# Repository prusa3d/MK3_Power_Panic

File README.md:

# MK3 Power Panic
KiCad PCB layout

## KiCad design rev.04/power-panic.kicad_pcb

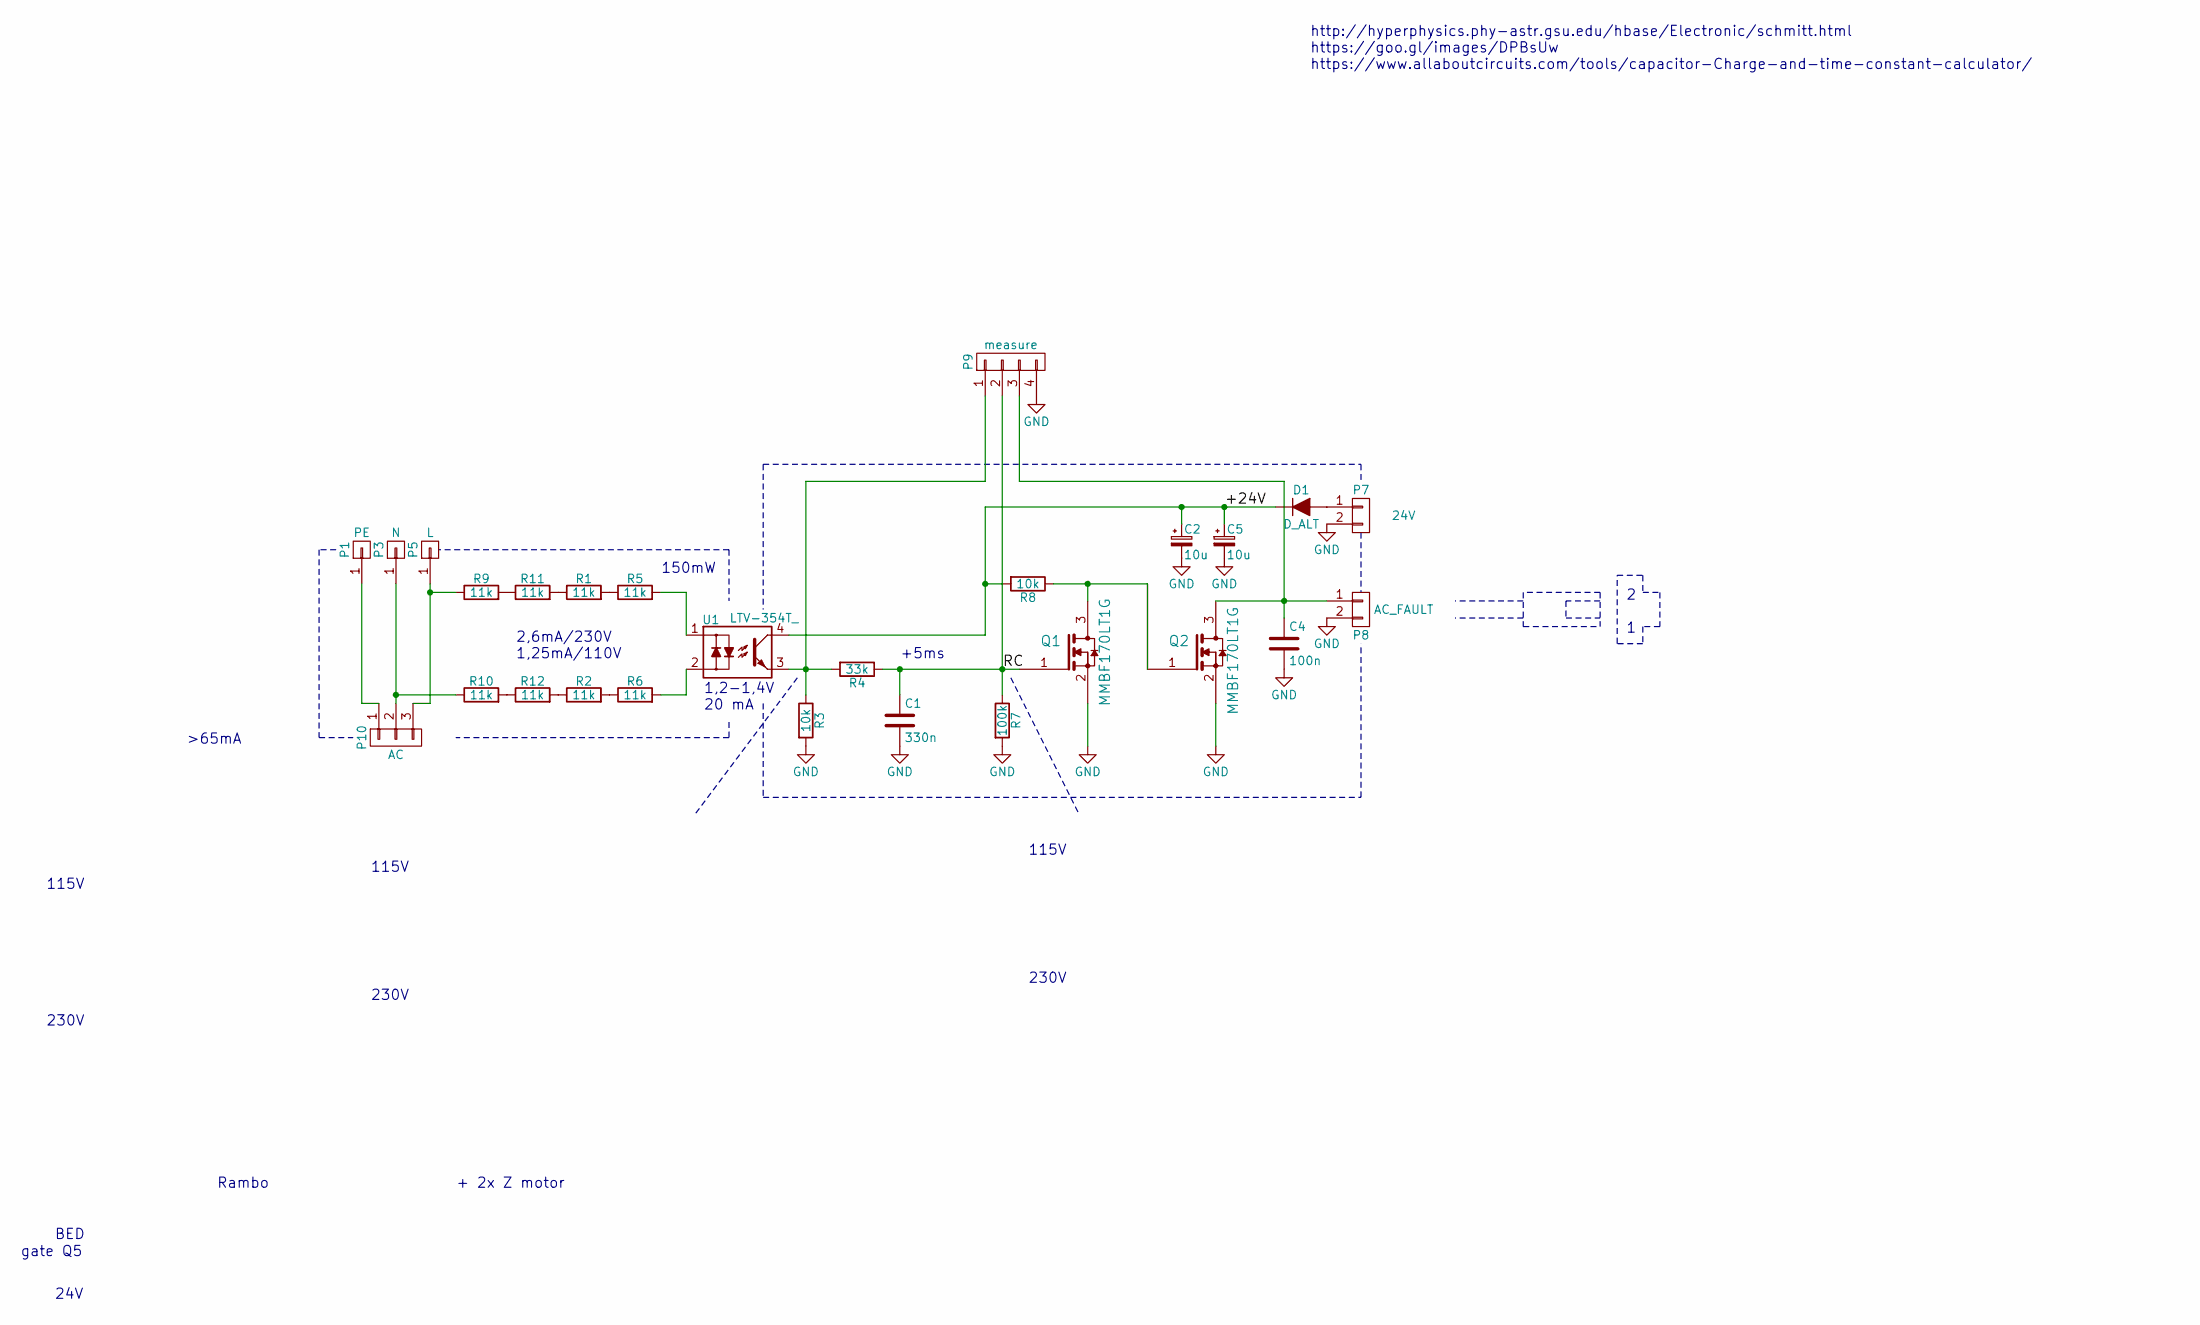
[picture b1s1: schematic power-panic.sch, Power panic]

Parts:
C1: 330n; C_0805
C2, C5: 10u; C_1206
C4: 100n; C_0805
D1: D_ALT; SOD-323
P1: PE; faston-hole-m
P3: N; faston-hole-m
P5: L; faston-hole-m
P7: 24V; Pin_1x02-XL
P8: AC_FAULT; Pin_1x02-XL
P9: measure; Pin_Header_Straight_1x04
P10: AC; ac-power-plug-fuse
Q1, Q2: MMBF170LT1G; SOT-23
R1, R2, R5, R6, R9, R10, R11, R12: 11k; R_1206
R3, R8: 10k; R_0805
R4: 33k; R_0805
R7: 100k; R_0805
U1: LTV-354T_; Optocoupler_SMD_LTV-817S

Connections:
/+24V: C2.1, C5.1, D1.1 (K), R8.2, U1.4
/RC: C1.1, P9.2, Q1.1, R4.1, R7.1
GND: C1.2, C2.2, C4.2, C5.2, P7.2, P8.2, P9.4, Q1.2, Q2.2, R3.2, R7.2
unnamed: C4.1, P8.1, P9.3, Q2.3
unnamed: D1.2 (A), P7.1
unnamed: P1.1, P10.1
unnamed: P9.1, R3.1, R4.2, U1.3
unnamed: P3.1, P10.2, R10.1
unnamed: P5.1, P10.3, R9.1
unnamed: Q1.3, Q2.1, R8.1
unnamed: R1.1, R11.2
unnamed: R1.2, R5.1
unnamed: R2.2, R6.1
unnamed: R5.2, U1.1
unnamed: R6.2, U1.2
unnamed: R10.2, R12.1
unnamed: R9.2, R11.1
unnamed: R2.1, R12.2

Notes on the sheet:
2,6mA/230V 1,25mA/110V
150mW
http://hyperphysics.phy-astr.gsu.edu/hbase/Electronic/schmitt.html https://goo.gl/images/DPBsUw https://www.allaboutcircuits.com/tools/capacitor-Charge-and-time-constant-calculator/
1,2-1,4V 20 mA
+5ms
115V
230V
>65mA
Rambo
+ 2x Z motor
24V
BED
gate Q5
2 1

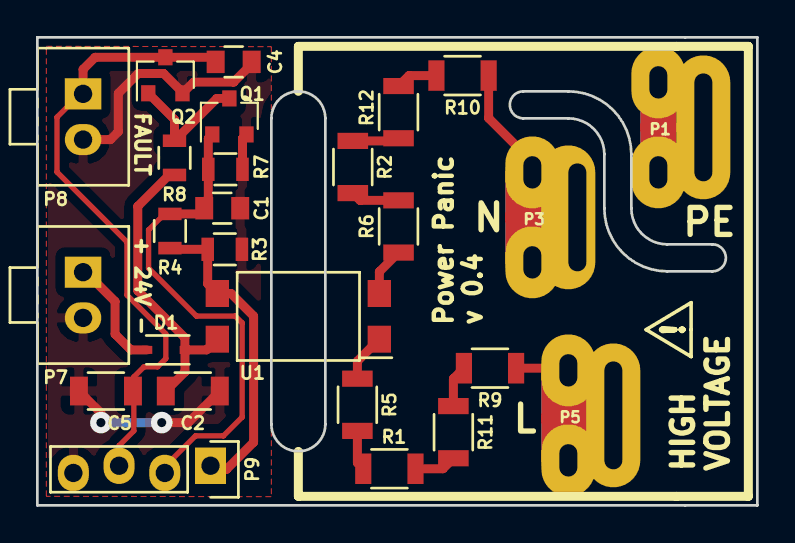
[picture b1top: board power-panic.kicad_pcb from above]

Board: 2 copper layers, 40.0 x 26.0 mm, 27 parts (1 on the bottom side), 18 nets.

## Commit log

2017-12-01 rev.04
2019-08-19 delta
